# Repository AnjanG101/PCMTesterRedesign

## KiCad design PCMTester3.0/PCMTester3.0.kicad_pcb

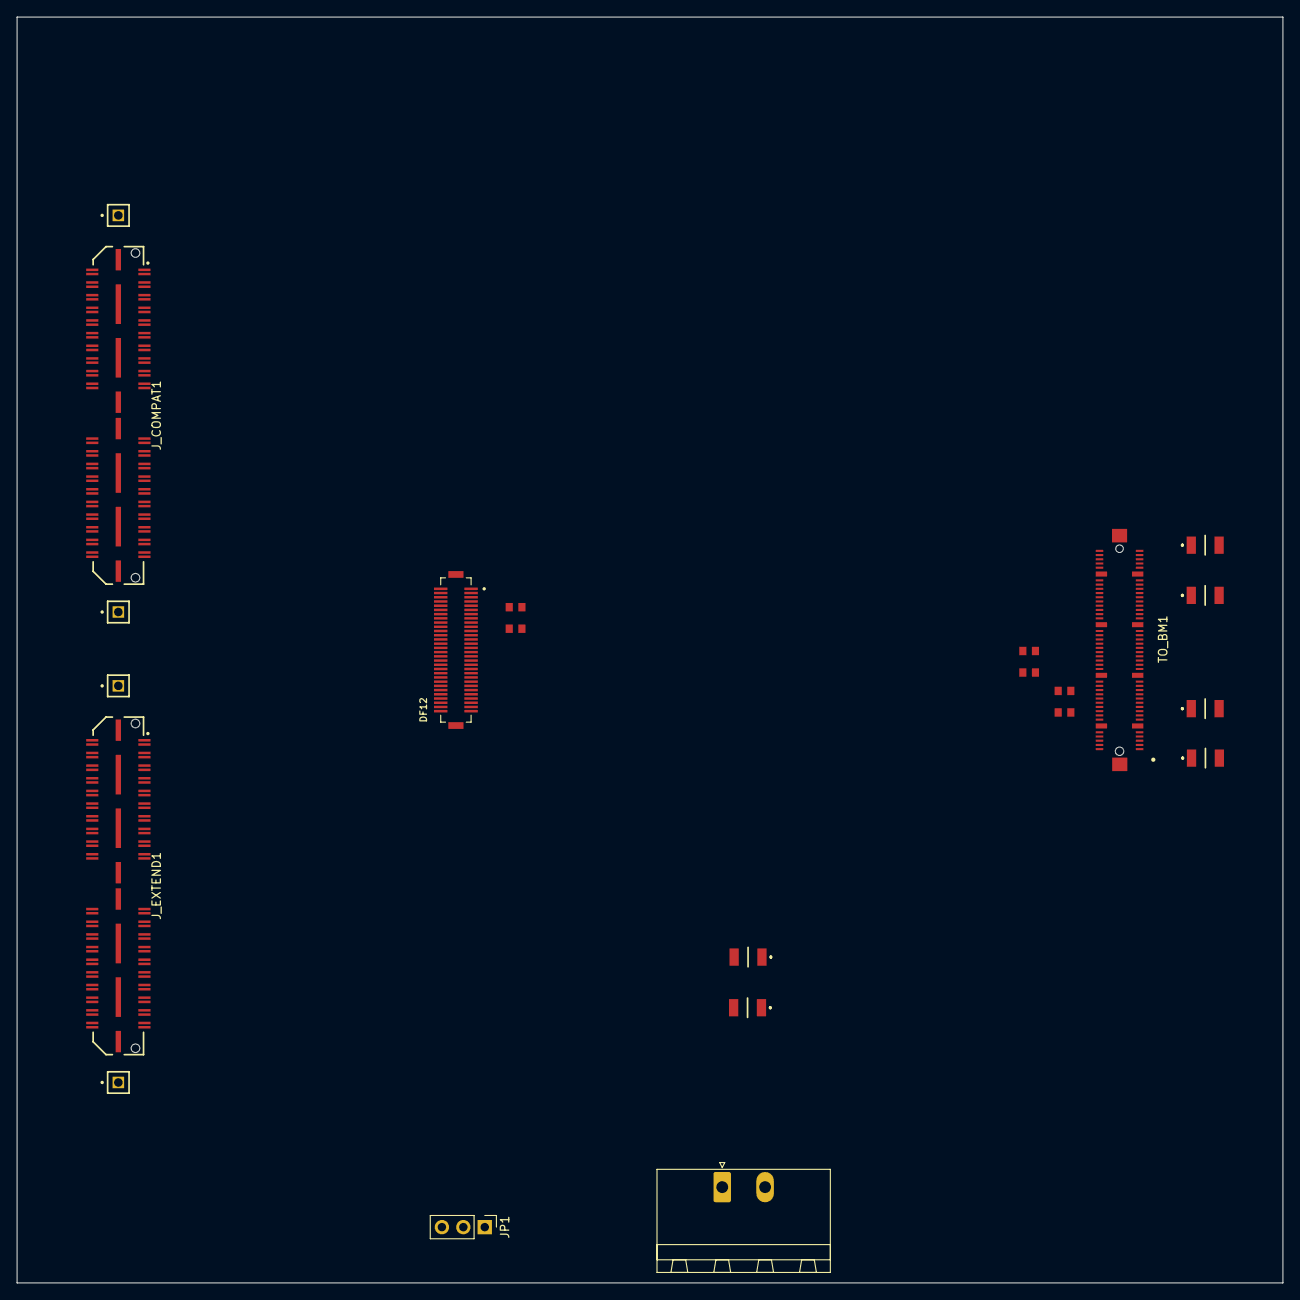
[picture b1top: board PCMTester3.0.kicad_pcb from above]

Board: 6 copper layers, 150.0 x 150.0 mm, 22 parts (0 on the bottom side), 36 nets, no tracks yet.

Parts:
C1, C2, C3, C4, C5, C6: 22uF; 22uF_Capacitor
DF12: DF12 connector for HGCAL test boards for partial 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; HRS_DF12NB-60DS-0.5V_51_
JP1: Jumper_3_Open; PinHeader_1x03_P2.54mm_Vertical
J_COMPAT1: Samtec QTH-040; SAMTEC_QTH-040-01-L-D-DP-A
J_EXTEND1: Samtec QTH-040; SAMTEC_QTH-040-01-L-D-DP-A
PWR_CORE1: power_conn; PhoenixContact_MSTB_2,5_2-GF-5,08_1x02_P5.08mm_Horizontal_T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
R1, R2, R3, R4, R5, R6: ERJ-3EKF1002V; RESC1608X50N
TO_BM1: FX11A-80P8; HIROSE_FX11A-80P-8-SV
TP1, TP2, TP3: Samtec TSW-101-07-G-S; SAMTEC_TSW-101-07-G-S (pin)
TP_VBRD1: Samtec TSW-101-07-G-S; SAMTEC_TSW-101-07-G-S (pin)

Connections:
/3V3D: JP1.3 (B), J_COMPAT1.6, J_COMPAT1.8, J_COMPAT1.10, J_COMPAT1.12, J_COMPAT1.14, J_COMPAT1.16, J_COMPAT1.18, J_COMPAT1.20, J_COMPAT1.22, J_COMPAT1.24, J_COMPAT1.26, J_COMPAT1.28, J_EXTEND1.38, J_EXTEND1.40
/BM28_HGCROC_RE_HB: J_EXTEND1.62, TO_BM1.52
/BM28_I2C_SCL: J_EXTEND1.65, TO_BM1.12
/BM28_I2C_SDA: J_EXTEND1.67, TO_BM1.16
/BM28_PG_LDO: J_EXTEND1.64, TO_BM1.60
/BM28_PROBE_DC: J_EXTEND1.77, TO_BM1.65
/BM28_PWR_EN_LDO: J_EXTEND1.66, TO_BM1.64
/BM28_RTD: J_EXTEND1.80, TO_BM1.69
/BM28_RTD_REF: J_EXTEND1.78, TO_BM1.73
/BM28_S1_HGCROC_RE_SB: J_EXTEND1.45, TO_BM1.46
/BM28_S2_HGCROC_RE_SB: J_EXTEND1.47, TO_BM1.50
/BM28_VMON_LVS: J_EXTEND1.68, TO_BM1.68
/DF12_HGCROC_RE_HB: DF12.31 (HGCROC_RE_HB), J_EXTEND1.35
/DF12_I2C_SCL: DF12.7 (I2C_SCL), J_EXTEND1.61, R1.2
/DF12_I2C_SDA: DF12.9 (I2C_SDA), J_EXTEND1.63, R2.2
/DF12_PG_LDO: DF12.33 (PG_LDO), J_EXTEND1.34
/DF12_PWR_EN_LDO: DF12.37 (PWR_EN), J_EXTEND1.42
/DF12_RTD: DF12.45 (RTD), J_EXTEND1.50
/DF12_RTD_REF: DF12.47 (RTD_REF), J_EXTEND1.52
/DF12_S1_HGCROC_RE_SB: DF12.39 (S1_HGCROC_RE_SB), J_EXTEND1.44
/DF12_S1_PROBE_DC: DF12.41 (S1_PROBE_DC), J_EXTEND1.46
/DF12_S2_HGCROC_RE_SB: DF12.29 (S2_HGCROC_RE_SB), J_EXTEND1.33
/DF12_S2_PROBE_DC: DF12.27 (S2_PROBE_DC), J_EXTEND1.31
/DF12_VMON_LVS: DF12.35 (VMON_LVS), J_EXTEND1.36
/ECON_D_ERROR_B: J_EXTEND1.5, TO_BM1.20
/ECON_D_RESET_B: J_COMPAT1.72, R3.1, TO_BM1.24
/ECON_D_SOFT_RESET_B: J_COMPAT1.78, R5.1, TO_BM1.34
/ECON_T_RESET_B: J_COMPAT1.70, R4.1, TO_BM1.28
/ECON_T_SOFT_RESET_B: J_COMPAT1.80, R6.1, TO_BM1.38
/MGND: J_EXTEND1.3, TO_BM1.77
/S1_ERR: DF12.43 (S1_ERR), J_EXTEND1.48
/S2_ERR: DF12.25 (S2_ERR), J_EXTEND1.29
/VADJ: J_EXTEND1.37, J_EXTEND1.39
GND: C1.2, C2.2, C3.1, C4.1, C5.1, C6.1, DF12.5 (GND), DF12.6 (GND), DF12.12 (GND), DF12.18 (GND), DF12.24 (GND), DF12.30 (GND), DF12.36 (GND), DF12.42 (GND), DF12.48 (GND), DF12.49 (GND), DF12.54 (GND), DF12.55 (GND), DF12.60 (GND), J_COMPAT1.2, J_COMPAT1.4, J_COMPAT1.13, J_COMPAT1.15, J_COMPAT1.17, J_COMPAT1.19, J_COMPAT1.33, J_COMPAT1.35, J_COMPAT1.37, J_COMPAT1.G1 (GND), J_COMPAT1.G2 (GND), J_COMPAT1.G3 (GND), J_COMPAT1.G4 (GND), J_COMPAT1.G5 (GND), J_COMPAT1.G6 (GND), J_COMPAT1.G7 (GND), J_COMPAT1.G8 (GND), J_EXTEND1.G1 (GND), J_EXTEND1.G2 (GND), J_EXTEND1.G3 (GND), J_EXTEND1.G4 (GND), J_EXTEND1.G5 (GND), J_EXTEND1.G6 (GND), J_EXTEND1.G7 (GND), J_EXTEND1.G8 (GND), PWR_CORE1.2 (NEG), TO_BM1.4, TO_BM1.5, TO_BM1.8, TO_BM1.9, TO_BM1.13, TO_BM1.14, TO_BM1.17, TO_BM1.18, TO_BM1.21, TO_BM1.22, TO_BM1.25, TO_BM1.26, TO_BM1.30, TO_BM1.32, TO_BM1.33, TO_BM1.36, TO_BM1.37, TO_BM1.40, TO_BM1.41, TO_BM1.44, TO_BM1.45, TO_BM1.48, TO_BM1.49, TO_BM1.54, TO_BM1.55, TO_BM1.58, TO_BM1.59, TO_BM1.62, TO_BM1.63, TO_BM1.66, TO_BM1.67, TO_BM1.70, TO_BM1.71, TO_BM1.72, TO_BM1.75, TO_BM1.76, TO_BM1.79, TO_BM1.80, TO_BM1.81 (SHELL), TO_BM1.82 (SHELL), TO_BM1.83 (SHELL), TO_BM1.84 (SHELL), TO_BM1.85 (SHELL), TO_BM1.86 (SHELL), TO_BM1.87 (SHELL), TO_BM1.88 (SHELL), TO_BM1.GND1, TO_BM1.GND2
unnamed: JP1.1 (A), PWR_CORE1.1 (POS)
VDD: C1.1, C2.1, C3.2, C4.2, C5.2, C6.2, DF12.11 (P1V2D), DF12.13 (P1V2D), DF12.15 (P1V2D), DF12.17 (P1V2D), DF12.19 (P1V2D), DF12.21 (P1V2D), DF12.23 (P1V2D), JP1.2 (C), R1.1, R2.1, R3.2, R4.2, R5.2, R6.2, TO_BM1.27, TO_BM1.29, TO_BM1.31

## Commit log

2025-07-16 Init files
2025-07-16 original design
2025-07-16 adding new pcm tester board
2025-07-16 board 2.0
2025-07-16 adding new design footprints and schematic
2025-07-17 new pcb design with components laid out
2025-07-17 Version 3.0
2025-07-17 component layout on board
2025-07-17 added ground and power planes
2025-07-17 re-adding version 3.0
2025-07-17 power plane with jumper and ground plane
2025-07-17 adding schematic with updated DF12 pins
2025-07-17 version 4.0
2025-07-17 stibbin it
2025-07-17 FINAL VERSION
2025-07-18 ts buss
2025-07-18 added ground and power (w/ jumpers) planes as well as all the ground and power conn. and the capacitors. Also added half of the mounting holes
